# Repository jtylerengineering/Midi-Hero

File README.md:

# Midi-Hero

## Description
The MIDI-Hero is a custom MIDI that mimics a *Guitar Hero* controller that was created as a Week 3 submission for Hack Club's ten week long Half Life event. The board is powered by a Waveshare ESP32 S3 microcontroller with <a href="https://github.com/KMKfw/kmk_firmware/blob/main/docs/en/README.md">KMK</a> for firmware.

## Requirements
### Hardware
#### Component BOM
Below is a list of components you will need, and where I sourced them from.

| Component | Units (how many of each set you will have to buy) | Price per unit | Source | Shipping |
| --- | --- | --- | --- | --- |
| PCB | 1 | $8.80 | <a href="https://jlcpcb.com/">JLPCB</a> | 
| Keyboard Switch | 1 | 0.65 | <a href ="https://www.aliexpress.com/item/3256806385705423.html?spm=a2g0o.cart.0.0.618e38da4EeBiV&mp=1&pdp_npi=6%40dis%21USD%21USD%200.65%21USD%200.47%21%21USD%200.47%21%21%21%402101e80b17929768393442096e0ebc%2112000037704740809%21ct%21US%218282019388%21%211%210%21&_gl=1*jx3zfr*_gcl_aw*R0NMLjE3OTI1ODUxNzAuQ2p3S0NBanc1NnpXQmhCMEVpd0FkUE9RT2RLQnpWQTdQcnZsamVPZG4wN2ozaWRWVmZHLXhPNldWM1VNSnRFUW9aVGVzRElPT3pCbDhSb0MyS2dRQXZEX0J3RQ..*_gcl_dc*R0NMLjE3OTI1ODUxNzAuQ2p3S0NBanc1NnpXQmhCMEVpd0FkUE9RT2RLQnpWQTdQcnZsamVPZG4wN2ozaWRWVmZHLXhPNldWM1VNSnRFUW9aVGVzRElPT3pCbDhSb0MyS2dRQXZEX0J3RQ..*_gcl_au*NTU4NjE1ODIxLjE3OTI5NjU2NTA.*_ga*MjEzMzg5NTIwLjE3OTI5NzY2Mjk.*_ga_VED1YSGNC7*czE3OTI5NzY2MjkkbzEkZzEkdDE3OTI5NzY5NjUkajYwJGwwJGgw">Aliexpress</a> |
| Rotary Encoder | 1 | $2.30 |<a href ="[https://www.aliexpress.us/item/3256806414004024.html?spm=a2g0o.cart.0.0.618e38daTn9NyX&mp=1&pdp_npi=6%40dis%21USD%21USD+2.30%21USD+2.30%21%21USD+2.30%21%21%21%4021032e4e17929766291257345e0ef1%2112000037782871490%21ct%21US%218282019388%21%211%210%21&_gl=1*1kr33bv*_gcl_aw*R0NMLjE3OTI1ODUxNzAuQ2p3S0NBanc1NnpXQmhCMEVpd0FkUE9RT2RLQnpWQTdQcnZsamVPZG4wN2ozaWRWVmZHLXhPNldWM1VNSnRFUW9aVGVzRElPT3pCbDhSb0MyS2dRQXZEX0J3RQ..*_gcl_dc*R0NMLjE3OTI1ODUxNzAuQ2p3S0NBanc1NnpXQmhCMEVpd0FkUE9RT2RLQnpWQTdQcnZsamVPZG4wN2ozaWRWVmZHLXhPNldWM1VNSnRFUW9aVGVzRElPT3pCbDhSb0MyS2dRQXZEX0J3RQ..*_gcl_au*NTU4NjE1ODIxLjE3OTI5NjU2NTA.*_ga*MjEzMzg5NTIwLjE3OTI5NzY2Mjk.*_ga_VED1YSGNC7*czE3OTI5NzY2MjkkbzEkZzAkdDE3OTI5NzY2MjkkajYwJGwwJGgw&gatewayAdapt=glo2usa](https://www.aliexpress.us/item/3256813007942184.html?spm=a2g0o.cart.0.0.618e38da4EeBiV&mp=1&pdp_npi=6%40dis%21USD%21USD+2.29%21USD+2.29%21%21USD+2.29%21%21%21%402101e80b17929768630603039e0ebc%2112000060523754199%21ct%21US%218282019388%21%211%210%21&_gl=1*n93ae7*_gcl_aw*R0NMLjE3OTI1ODUxNzAuQ2p3S0NBanc1NnpXQmhCMEVpd0FkUE9RT2RLQnpWQTdQcnZsamVPZG4wN2ozaWRWVmZHLXhPNldWM1VNSnRFUW9aVGVzRElPT3pCbDhSb0MyS2dRQXZEX0J3RQ..*_gcl_dc*R0NMLjE3OTI1ODUxNzAuQ2p3S0NBanc1NnpXQmhCMEVpd0FkUE9RT2RLQnpWQTdQcnZsamVPZG4wN2ozaWRWVmZHLXhPNldWM1VNSnRFUW9aVGVzRElPT3pCbDhSb0MyS2dRQXZEX0J3RQ..*_gcl_au*NTU4NjE1ODIxLjE3OTI5NjU2NTA.*_ga*MjEzMzg5NTIwLjE3OTI5NzY2Mjk.*_ga_VED1YSGNC7*czE3OTI5NzY2MjkkbzEkZzEkdDE3OTI5NzY4MzkkajYwJGwwJGgw&gatewayAdapt=glo2usa)">Aliexpress</a> |
| PS2 Joystick | 1 | $3.02 | <a href="https://www.aliexpress.us/item/3256805763176642.html?spm=a2g0o.cart.0.0.618e38da4EeBiV&mp=1&pdp_npi=6%40dis%21USD%21USD+3.02%21USD+3.02%21%21USD+3.02%21%21%21%402101e80b17929768630603039e0ebc%2112000035000335220%21ct%21US%218282019388%21%211%210%21&_gl=1*7f4qeu*_gcl_aw*R0NMLjE3OTI1ODUxNzAuQ2p3S0NBanc1NnpXQmhCMEVpd0FkUE9RT2RLQnpWQTdQcnZsamVPZG4wN2ozaWRWVmZHLXhPNldWM1VNSnRFUW9aVGVzRElPT3pCbDhSb0MyS2dRQXZEX0J3RQ..*_gcl_dc*R0NMLjE3OTI1ODUxNzAuQ2p3S0NBanc1NnpXQmhCMEVpd0FkUE9RT2RLQnpWQTdQcnZsamVPZG4wN2ozaWRWVmZHLXhPNldWM1VNSnRFUW9aVGVzRElPT3pCbDhSb0MyS2dRQXZEX0J3RQ..*_gcl_au*NTU4NjE1ODIxLjE3OTI5NjU2NTA.*_ga*MjEzMzg5NTIwLjE3OTI5NzY2Mjk.*_ga_VED1YSGNC7*czE3OTI5NzY2MjkkbzEkZzEkdDE3OTI5NzY4NzMkajI2JGwwJGgw&gatewayAdapt=glo2usa">Aliexpress</a> |
| tax/shipping | $8.70 | --- | --- | --- |
| total | $30.08 |

#### Other
Other than the above, you will need:
1. The PCB. I used JLPCB for manufacturing, but whatever service fits your fancy will do.
2. Soldering supplies (iron, solder, etc.)
3. A computer to work with the firmware
4. a 3d printer for keycaps, case, etc.

### Firmware

## Assembly
>[!note]
>A full set of assembly instructions will be released during week 8, once I have photos.

### Electrical Parts

This is the number of each component from the 'Requirements' section you will need for one assembly per the current version.

| Component | Quantity |
| --- | --- |
| PCB | 1 |
| Keyboard Switch | 5 |
| Waveshare ESP32-S3 | 1 |
| PS2 Joystick | 1 |
| Rotary encoder | 1 |

### 3D printing
If you want the case and keycaps, you will need to either print them yourself or get them printed. I used PLA for my filament. Something to keep in mind, however, is that you will need a 0.2 mm nozzle for your printer. the tolerance needs to be rather tight, and you won't get that very well with a 0.4 mm nozzle.
All of the STL files are in the STL folder.

## Quick Links
**Most links are closed until week 8, to ensure that the final product is functioning as well as possible**
[Onshape Link-- closed]()

[MakerWorld Project-- closed]()

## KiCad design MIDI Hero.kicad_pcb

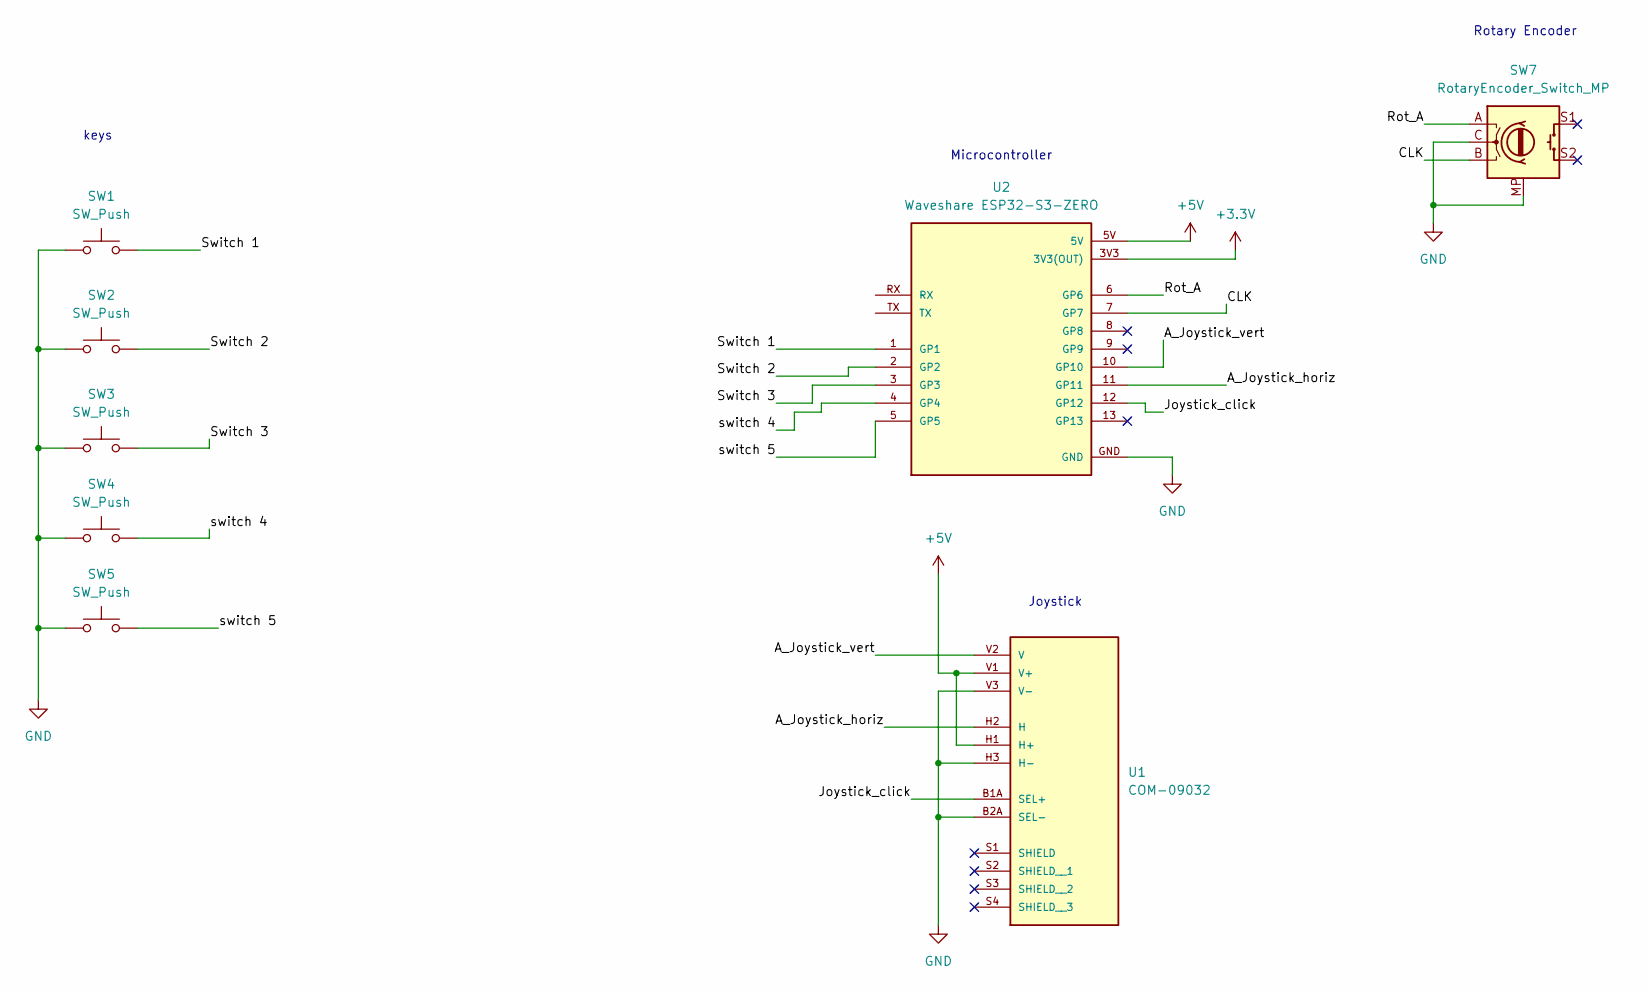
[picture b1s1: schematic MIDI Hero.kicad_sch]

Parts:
SW1, SW2, SW3, SW4, SW5: SW_Push; SW_Cherry_MX_1.00u_PCB
SW7: RotaryEncoder_Switch_MP; RotaryEncoder_Alps_EC11E-Switch_Vertical_H20mm
U1: COM-09032; XDCR_COM-09032; PARTREV N/A
U2: Waveshare ESP32-S3-ZERO; Waveshare ESP32-S3-Zero; PARTREV NA

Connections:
+3.3V: U2.3V3 (3V3(OUT))
+5V: U1.H1 (H+), U1.V1 (V+), U2.5V
/A_Joystick_horiz: U1.H2 (H), U2.11 (GP11)
/A_Joystick_vert: U1.V2 (V), U2.10 (GP10)
/CLK: SW7.B, U2.7 (GP7)
/Joystick_click: U1.B1A (SEL+), U2.12 (GP12)
/Rot_A: SW7.A, U2.6 (GP6)
/Switch 1: SW1.2, U2.1 (GP1)
/Switch 2: SW2.2, U2.2 (GP2)
/Switch 3: SW3.2, U2.3 (GP3)
/switch 4: SW4.2, U2.4 (GP4)
/switch 5: SW5.2, U2.5 (GP5)
GND: SW1.1, SW2.1, SW3.1, SW4.1, SW5.1, SW7.C, SW7.MP, U1.B2A (SEL-), U1.H3 (H-), U1.V3 (V-), U2.GND

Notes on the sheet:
keys
Microcontroller
Rotary Encoder
Joystick

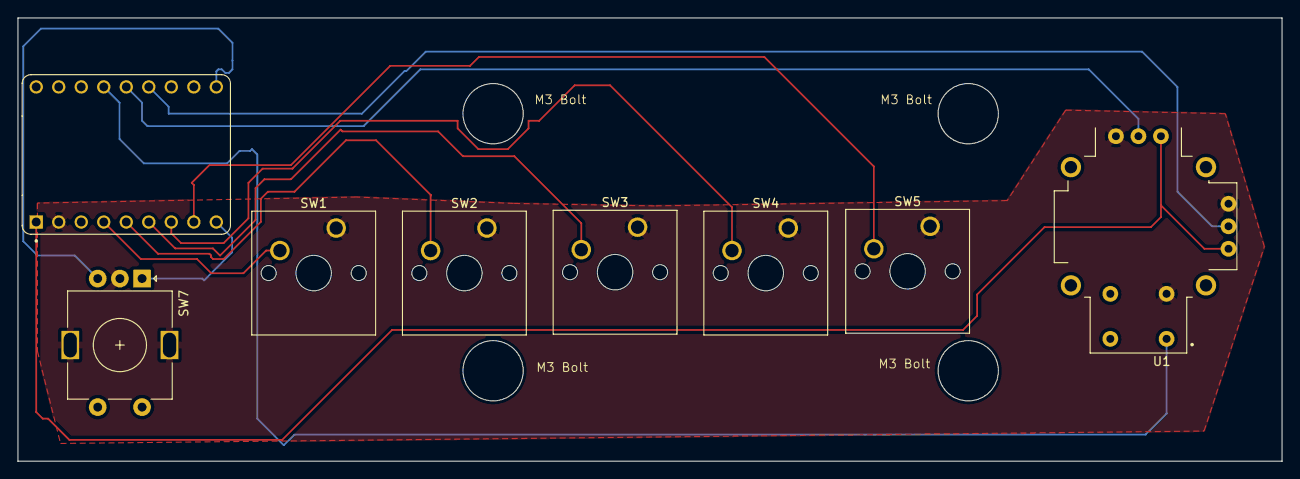
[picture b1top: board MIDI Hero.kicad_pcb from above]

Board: 2 copper layers, 142.6 x 50.0 mm, 8 parts (0 on the bottom side), 12 nets.
